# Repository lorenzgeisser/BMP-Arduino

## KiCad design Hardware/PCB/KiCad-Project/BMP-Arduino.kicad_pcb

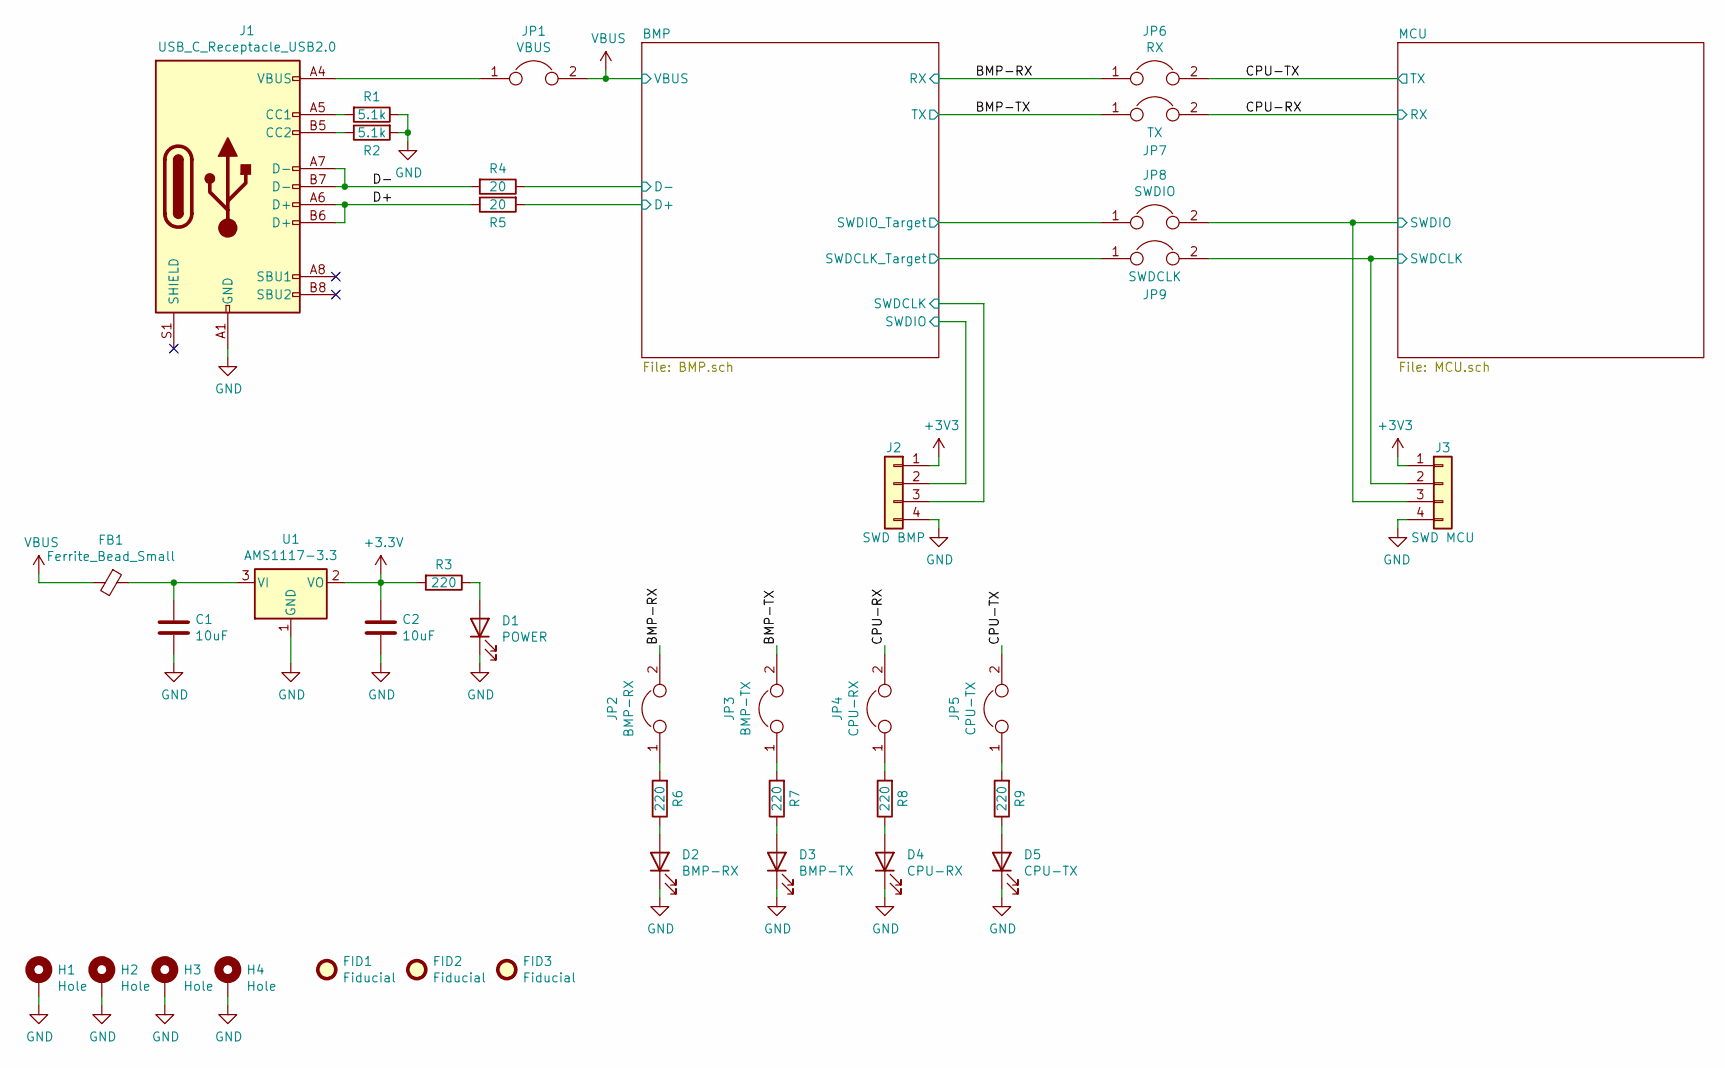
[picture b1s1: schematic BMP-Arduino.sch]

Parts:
C1, C2: 10uF; C_0603_1608Metric; LCSC Part # C19702
D1: POWER; LED_0603_1608Metric_Castellated; LCSC Part # C2286
D2: BMP-RX; LED_0603_1608Metric_Castellated; LCSC Part # C2286
D3: BMP-TX; LED_0603_1608Metric_Castellated; LCSC Part # C2286
D4: CPU-RX; LED_0603_1608Metric_Castellated; LCSC Part # C2286
D5: CPU-TX; LED_0603_1608Metric_Castellated; LCSC Part # C2286
FB1: Ferrite_Bead_Small; L_0805_2012Metric; LCSC Part # C1017
FID1, FID2, FID3: Fiducial; Fiducial_0.5mm_Mask1.5mm
H1, H2, H3, H4: Hole; MountingHole_2.7mm_Pad_Via
J1: USB_C_Receptacle_USB2.0; USB_C_Receptacle_HRO_TYPE-C-31-M-12
J2: SWD BMP; PinHeader_1x04_P2.54mm_Vertical
J3: SWD MCU; PinHeader_1x04_P2.54mm_Vertical
JP1: VBUS; PinHeader_1x02_P2.54mm_Vertical
JP2: BMP-RX; PinHeader_1x02_P2.54mm_Vertical
JP3: BMP-TX; PinHeader_1x02_P2.54mm_Vertical
JP4: CPU-RX; PinHeader_1x02_P2.54mm_Vertical
JP5: CPU-TX; PinHeader_1x02_P2.54mm_Vertical
JP6: RX; PinHeader_1x02_P2.54mm_Vertical
JP7: TX; PinHeader_1x02_P2.54mm_Vertical
JP8: SWDIO; PinHeader_1x02_P2.54mm_Vertical
JP9: SWDCLK; PinHeader_1x02_P2.54mm_Vertical
R1, R2: 5.1k; R_0603_1608Metric; LCSC Part # C23186
R3, R6, R7, R8, R9: 220; R_0603_1608Metric; LCSC Part # C22962
R4, R5: 20; R_0603_1608Metric; LCSC Part # C22950
U1: AMS1117-3.3; SOT-223-3_TabPin2; LCSC Part # C6186

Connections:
/BMP-RX: JP2.2, JP6.1; also elsewhere on the board
/BMP-TX: JP3.2, JP7.1; also elsewhere on the board
/BMP/D+: R5.2; also elsewhere on the board
/BMP/D-: R4.1; also elsewhere on the board
/BMP/SWDCLK: J2.3; also elsewhere on the board
/BMP/SWDCLK_Target: JP9.1; also elsewhere on the board
/BMP/SWDIO: J2.2; also elsewhere on the board
/BMP/SWDIO_Target: JP8.1; also elsewhere on the board
/CPU-RX: JP4.2, JP7.2; also elsewhere on the board
/CPU-TX: JP5.2, JP6.2; also elsewhere on the board
/D+: J1.A6 (D+), J1.B6 (D+), R5.1
/D-: J1.A7 (D-), J1.B7 (D-), R4.2
/MCU/SWDCLK: J3.2, JP9.2; also elsewhere on the board
/MCU/SWDIO: J3.3, JP8.2; also elsewhere on the board
GND: C1.2, C2.2, D1.1 (K), D2.1 (K), D3.1 (K), D4.1 (K), D5.1 (K), H1.1, H2.1, H3.1, H4.1, J1.A1 (GND), J1.A12 (GND), J1.B1 (GND), J1.B12 (GND), J2.4, J3.4, R1.1, R2.2, U1.1 (GND); also elsewhere on the board
unnamed: C1.1, FB1.1, U1.3 (VI)
unnamed: D1.2 (A), R3.1
unnamed: D2.2 (A), R6.1
unnamed: D3.2 (A), R7.1
unnamed: D4.2 (A), R8.1
unnamed: D5.2 (A), R9.1
unnamed: J1.A4 (VBUS), J1.A9 (VBUS), J1.B4 (VBUS), J1.B9 (VBUS), JP1.1
unnamed: J1.A5 (CC1), R1.2
unnamed: J1.B5 (CC2), R2.1
unnamed: JP2.1, R6.2
unnamed: JP3.1, R7.2
unnamed: JP4.1, R8.2
unnamed: JP5.1, R9.2
VBUS: FB1.2, JP1.2; also elsewhere on the board

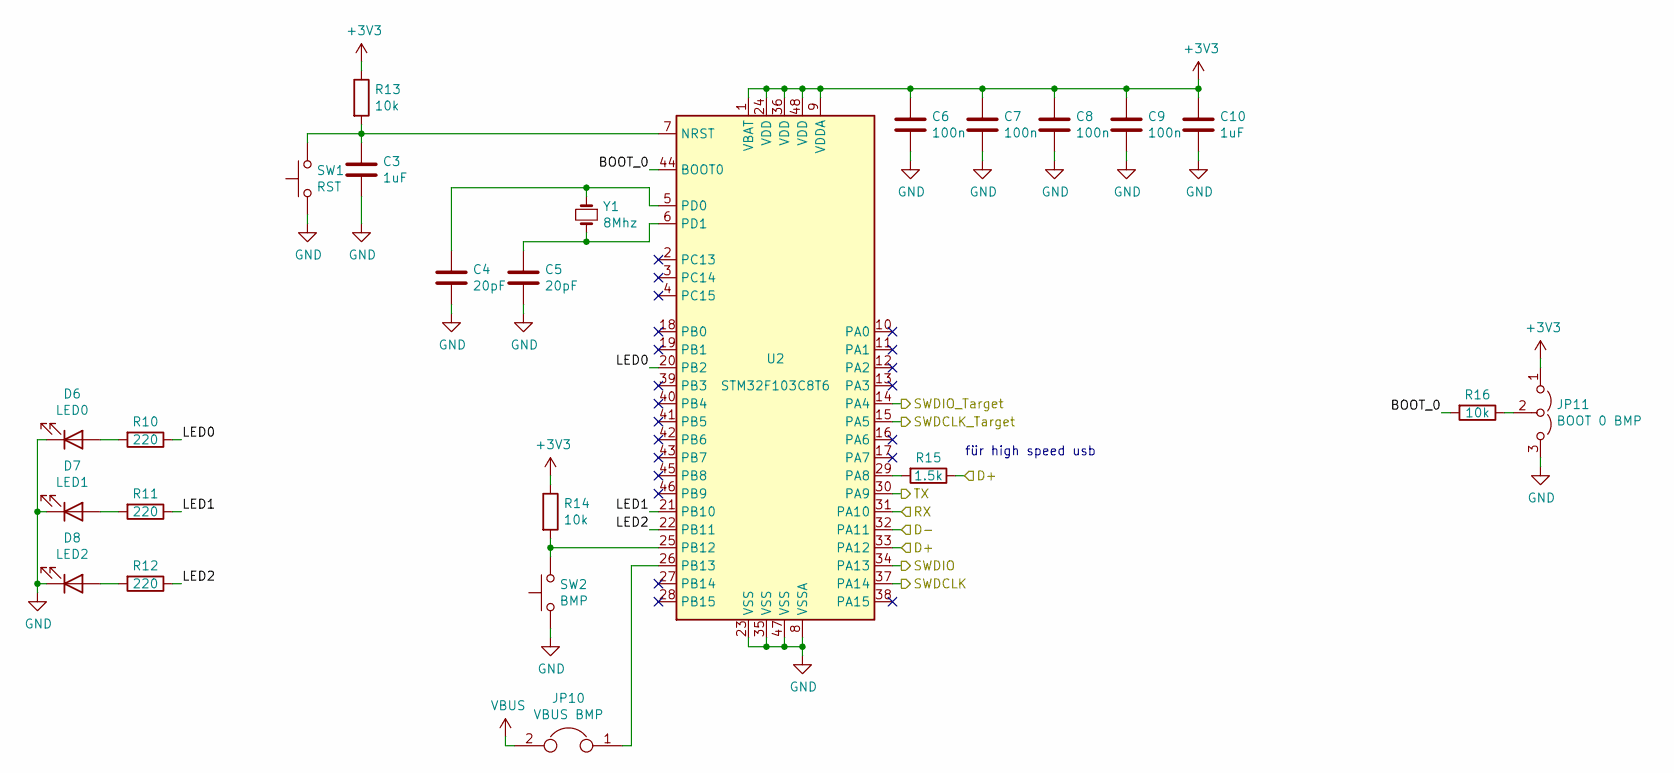
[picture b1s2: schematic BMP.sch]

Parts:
C3, C10: 1uF; C_0603_1608Metric; LCSC Part # C15849
C4, C5: 20pF; C_0603_1608Metric; LCSC Part # C1648
C6, C7, C8, C9: 100n; C_0603_1608Metric; LCSC Part # C14663
D6: LED0; LED_0603_1608Metric_Castellated; LCSC Part # C2286
D7: LED1; LED_0603_1608Metric_Castellated; LCSC Part # C2286
D8: LED2; LED_0603_1608Metric_Castellated; LCSC Part # C2286
JP10: VBUS BMP; PinHeader_1x02_P2.54mm_Vertical
JP11: BOOT 0 BMP; PinHeader_1x03_P2.54mm_Vertical
R10, R11, R12: 220; R_0603_1608Metric; LCSC Part # C22962
R13, R14, R16: 10k; R_0603_1608Metric; LCSC Part # C25804
R15: 1.5k; R_0603_1608Metric; LCSC Part # C22843
SW1: RST; SW_PUSH_6mm_H5mm
SW2: BMP; SW_PUSH_6mm_H5mm
U2: STM32F103C8T6; LQFP-48_7x7mm_P0.5mm; LCSC Part # C8734
Y1: 8Mhz; Crystal_SMD_5032-2Pin_5.0x3.2mm; MPN TAXM8M4RDBCCT2T; LCSC Part # C115962

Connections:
/BMP-RX: U2.31 (PA10); also elsewhere on the board
/BMP-TX: U2.30 (PA9); also elsewhere on the board
/BMP/BOOT_0: R16.2, U2.44 (BOOT0)
/BMP/D+: R15.1, U2.33 (PA12); also elsewhere on the board
/BMP/D-: U2.32 (PA11); also elsewhere on the board
/BMP/LED0: R10.1, U2.20 (PB2)
/BMP/LED1: R11.1, U2.21 (PB10)
/BMP/LED2: R12.1, U2.22 (PB11)
/BMP/SWDCLK: U2.37 (PA14); also elsewhere on the board
/BMP/SWDCLK_Target: U2.15 (PA5); also elsewhere on the board
/BMP/SWDIO: U2.34 (PA13); also elsewhere on the board
/BMP/SWDIO_Target: U2.14 (PA4); also elsewhere on the board
GND: C3.2, C4.2, C5.2, C6.2, C7.2, C8.2, C9.2, C10.2, D6.1 (K), D7.1 (K), D8.1 (K), JP11.3 (B), SW1.1, SW2.1, U2.8 (VSSA), U2.23 (VSS), U2.35 (VSS), U2.47 (VSS); also elsewhere on the board
unnamed: C3.1, R13.2, SW1.2, U2.7 (NRST)
unnamed: C4.1, U2.5 (PD0), Y1.1
unnamed: C5.1, U2.6 (PD1), Y1.2
unnamed: D6.2 (A), R10.2
unnamed: D7.2 (A), R11.2
unnamed: D8.2 (A), R12.2
unnamed: JP10.1, U2.26 (PB13)
unnamed: JP11.2 (C), R16.1
unnamed: R14.2, SW2.2, U2.25 (PB12)
unnamed: R15.2, U2.29 (PA8)
VBUS: JP10.2; also elsewhere on the board

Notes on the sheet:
für high speed usb

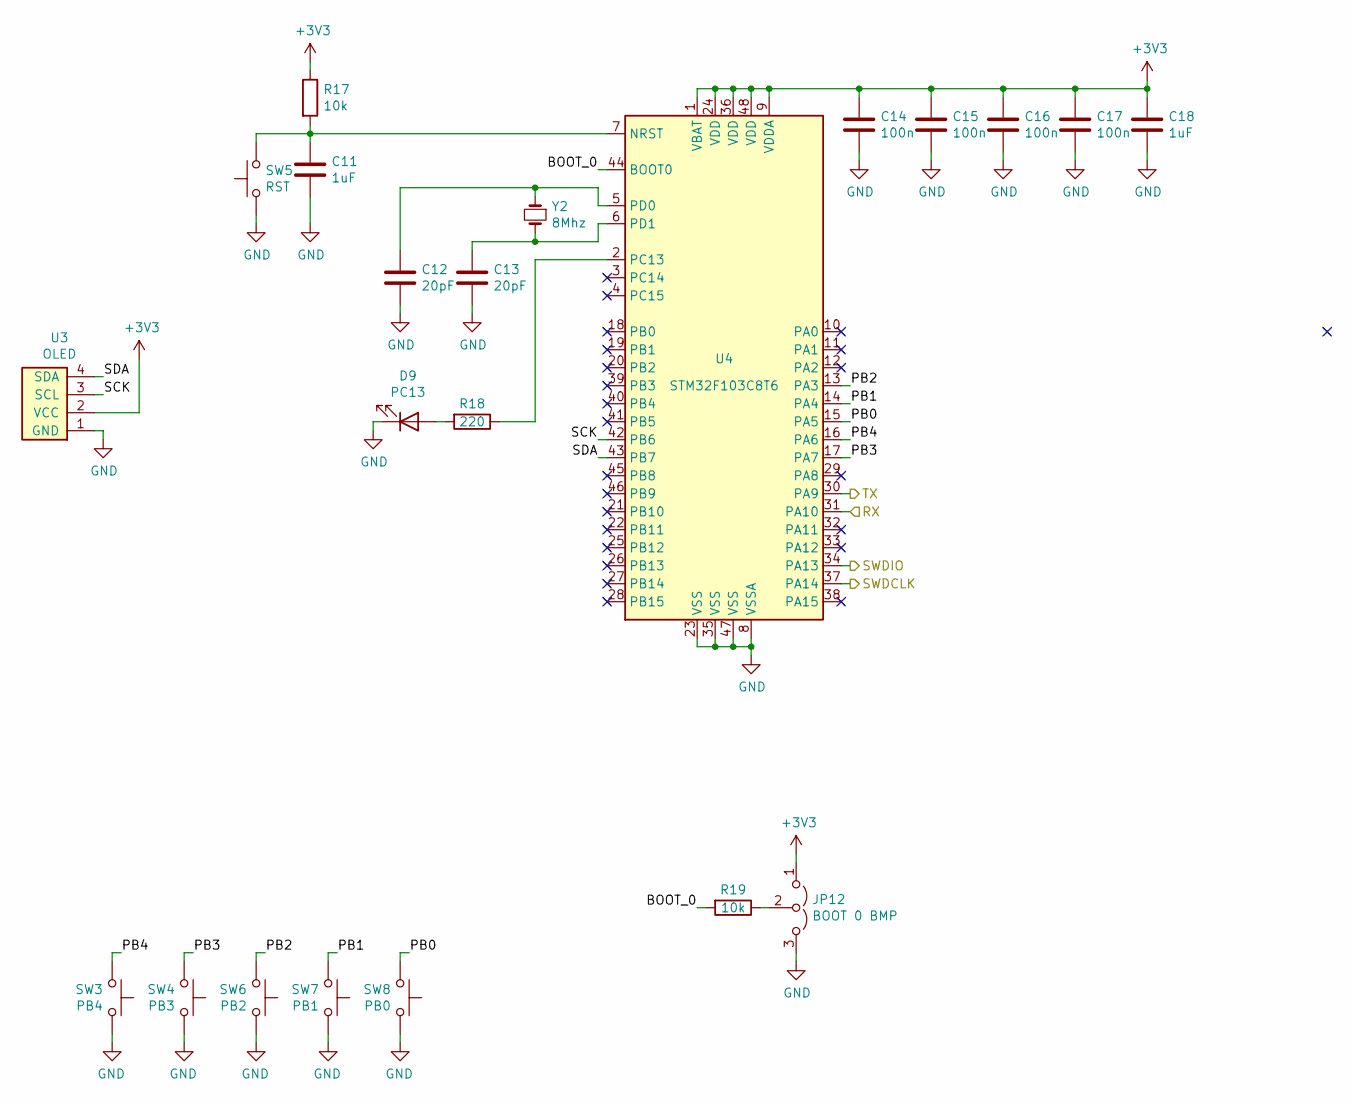
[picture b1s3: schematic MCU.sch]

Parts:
C11, C18: 1uF; C_0603_1608Metric; LCSC Part # C15849
C12, C13: 20pF; C_0603_1608Metric; LCSC Part # C1648
C14, C15, C16, C17: 100n; C_0603_1608Metric; LCSC Part # C14663
D9: PC13; LED_0603_1608Metric_Castellated; LCSC Part # C2286
JP12: BOOT 0 BMP; PinHeader_1x03_P2.54mm_Vertical
R17, R19: 10k; R_0603_1608Metric; LCSC Part # C25804
R18: 220; R_0603_1608Metric; LCSC Part # C22962
SW3: PB4; SW_PUSH_6mm_H5mm
SW4: PB3; SW_PUSH_6mm_H5mm
SW5: RST; SW_PUSH_6mm_H5mm
SW6: PB2; SW_PUSH_6mm_H5mm
SW7: PB1; SW_PUSH_6mm_H5mm
SW8: PB0; SW_PUSH_6mm_H5mm
U3: OLED
U4: STM32F103C8T6; LQFP-48_7x7mm_P0.5mm; LCSC Part # C8734
Y2: 8Mhz; Crystal_SMD_5032-2Pin_5.0x3.2mm; MPN TAXM8M4RDBCCT2T; LCSC Part # C115962

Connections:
/CPU-RX: U4.31 (PA10); also elsewhere on the board
/CPU-TX: U4.30 (PA9); also elsewhere on the board
/MCU/BOOT_0: R19.2, U4.44 (BOOT0)
/MCU/PB0: SW8.2, U4.15 (PA5)
/MCU/PB1: SW7.2, U4.14 (PA4)
/MCU/PB2: SW6.2, U4.13 (PA3)
/MCU/PB3: SW4.2, U4.17 (PA7)
/MCU/PB4: SW3.2, U4.16 (PA6)
/MCU/SCK: U3.3 (SCL), U4.42 (PB6)
/MCU/SDA: U3.4 (SDA), U4.43 (PB7)
/MCU/SWDCLK: U4.37 (PA14); also elsewhere on the board
/MCU/SWDIO: U4.34 (PA13); also elsewhere on the board
GND: C11.2, C12.2, C13.2, C14.2, C15.2, C16.2, C17.2, C18.2, D9.1 (K), JP12.3 (B), SW3.1, SW4.1, SW5.1, SW6.1, SW7.1, SW8.1, U3.1 (GND), U4.8 (VSSA), U4.23 (VSS), U4.35 (VSS), U4.47 (VSS); also elsewhere on the board
unnamed: C11.1, R17.2, SW5.2, U4.7 (NRST)
unnamed: C12.1, U4.5 (PD0), Y2.1
unnamed: C13.1, U4.6 (PD1), Y2.2
unnamed: D9.2 (A), R18.2
unnamed: JP12.2 (C), R19.1
unnamed: R18.1, U4.2 (PC13)

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
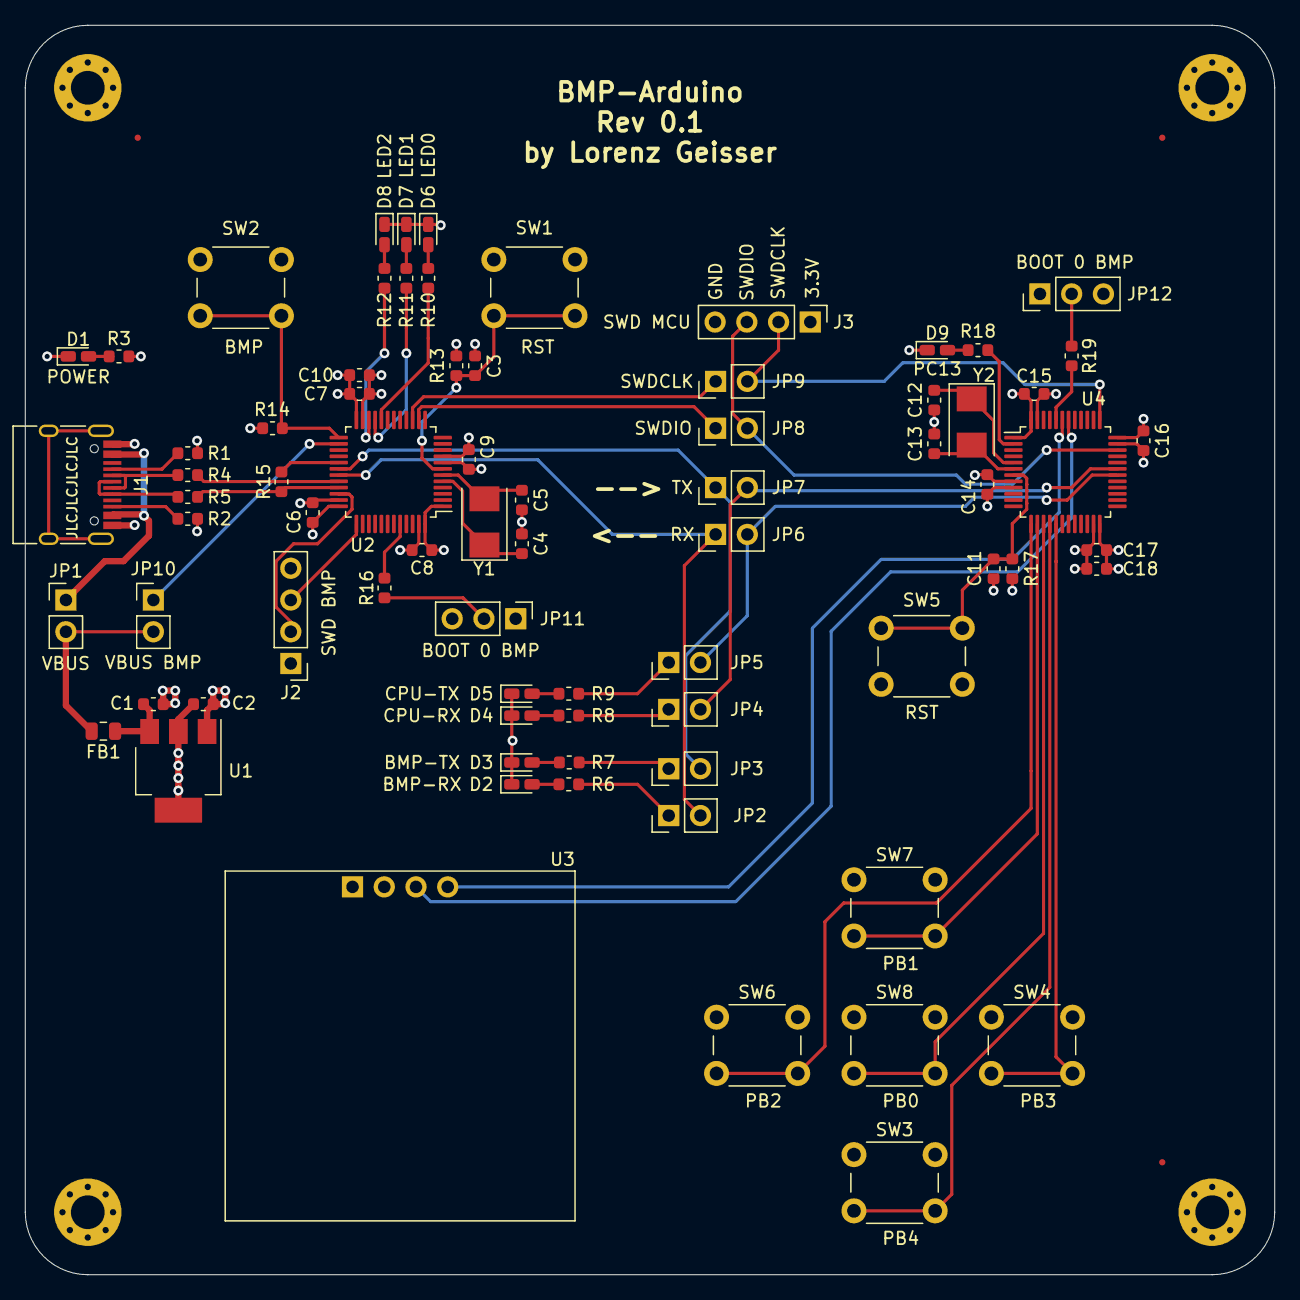
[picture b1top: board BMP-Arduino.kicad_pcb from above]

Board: 4 copper layers, 100.0 x 100.0 mm, 83 parts (0 on the bottom side), 58 nets.

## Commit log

2020-10-07 v0.1
2021-01-03 v1.0
